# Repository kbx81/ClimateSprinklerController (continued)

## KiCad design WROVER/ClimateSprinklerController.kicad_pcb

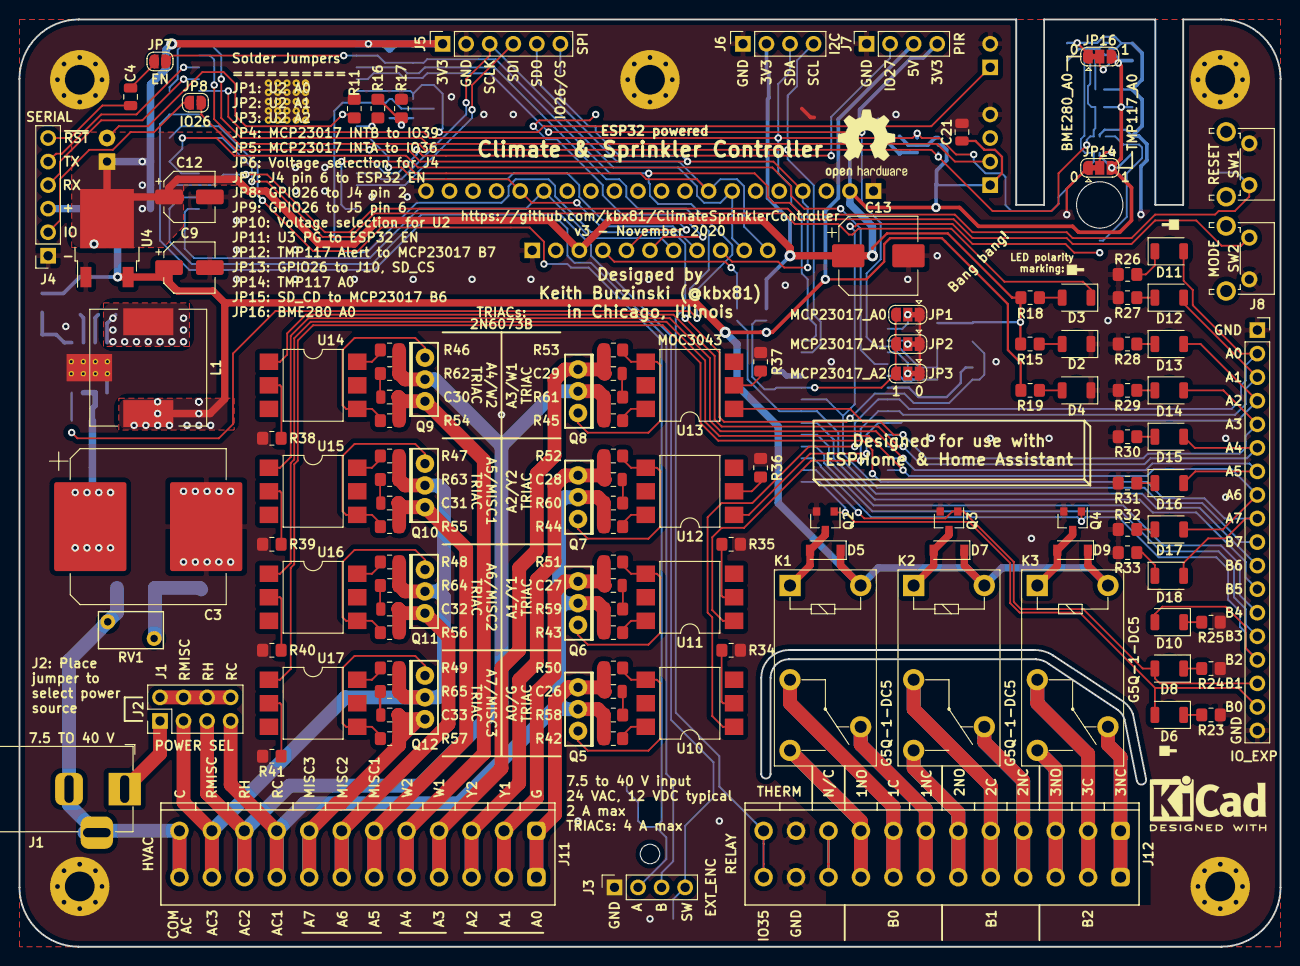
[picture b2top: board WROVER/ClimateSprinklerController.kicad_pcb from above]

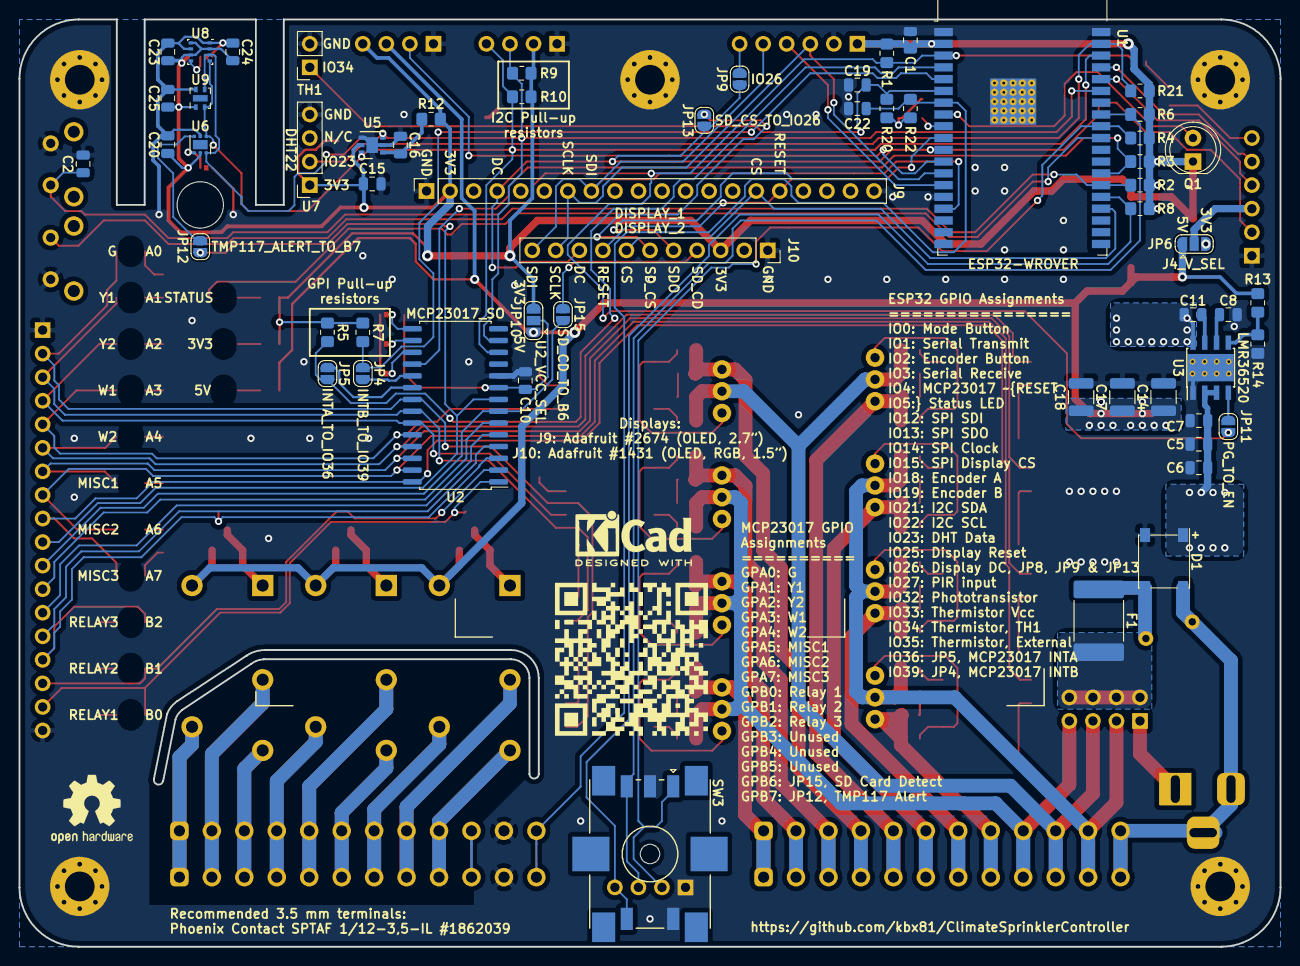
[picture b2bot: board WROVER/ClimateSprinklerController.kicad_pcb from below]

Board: 2 copper layers, 136.0 x 100.0 mm, 190 parts (61 on the bottom side), 141 nets.

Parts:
C1: 10 uF; C_0805_2012Metric
C2, C4, C10, C11, C19, C20, C21, C22, C23, C24, C25: 100 nF; C_0805_2012Metric
C3: 470 uF; CP_Elec_16x17.5
C5, C6: 4.7 uF; C_0805_2012Metric
C7: 220 nF; C_0805_2012Metric
C8, C15, C16: 1 uF; C_0805_2012Metric
C9, C12: 10 uF; CP_Elec_5x5.8
C13: 220 uF; CP_Elec_8x10
C14, C17, C18: 47 uF; C_1210_3225Metric
C26, C27, C28, C29, C30, C31, C32, C33: .01 uF; C_0805_2012Metric
D1: N/A; Diode_Bridge_Bourns_CD-MBL2xxS
D2: 3V3; LED_1206_3216Metric_ReverseMount_Hole1.8x2.4mm
D3: STATUS; LED_1206_3216Metric_ReverseMount_Hole1.8x2.4mm
D4: 5V; LED_1206_3216Metric_ReverseMount_Hole1.8x2.4mm
D5, D7, D9: N/A; D_SOD-123
D6: RELAY1; LED_1206_3216Metric_ReverseMount_Hole1.8x2.4mm
D8: RELAY2; LED_1206_3216Metric_ReverseMount_Hole1.8x2.4mm
D10: RELAY3; LED_1206_3216Metric_ReverseMount_Hole1.8x2.4mm
D11: G; LED_1206_3216Metric_ReverseMount_Hole1.8x2.4mm
D12: Y1; LED_1206_3216Metric_ReverseMount_Hole1.8x2.4mm
D13: Y2; LED_1206_3216Metric_ReverseMount_Hole1.8x2.4mm
D14: W1; LED_1206_3216Metric_ReverseMount_Hole1.8x2.4mm
D15: W2; LED_1206_3216Metric_ReverseMount_Hole1.8x2.4mm
D16: MISC1; LED_1206_3216Metric_ReverseMount_Hole1.8x2.4mm
D17: MISC2; LED_1206_3216Metric_ReverseMount_Hole1.8x2.4mm
D18: MISC3; LED_1206_3216Metric_ReverseMount_Hole1.8x2.4mm
F1: 300 mA; Fuse_2920_7451Metric
H1, H2, H3, H4, H5: MountingHole_Pad; MountingHole_3.2mm_M3_Pad_Via
H6: MountingHole; MountingHole_5mm
J1: 7.5 TO 40 V; BarrelJack_Horizontal
J2: POWER SEL; PinHeader_2x04_P2.54mm_Vertical
J3: EXT_ENC; PinSocket_1x04_P2.54mm_Vertical
J4: SERIAL; PinSocket_1x06_P2.54mm_Vertical
J5: SPI; PinSocket_1x06_P2.54mm_Vertical
J6: I2C; PinSocket_1x04_P2.54mm_Vertical
J7: PIR; PinSocket_1x04_P2.54mm_Vertical
J8: IO_EXP; PinSocket_1x18_P2.54mm_Vertical
J9: DISPLAY_1; PinSocket_1x20_P2.54mm_Vertical
J10: DISPLAY_2; PinSocket_1x11_P2.54mm_Vertical
J11: HVAC; PhoenixContact_SPTAF_1_12-3.5-IL_1x12_P3.50mm_Vertical
J12: RELAY; PhoenixContact_SPTAF_1_12-3.5-IL_1x12_P3.50mm_Vertical
JP1: MCP23017_A0; SolderJumper-3_P1.3mm_Bridged12_RoundedPad1.0x1.5mm
JP2: MCP23017_A1; SolderJumper-3_P1.3mm_Bridged12_RoundedPad1.0x1.5mm
JP3: MCP23017_A2; SolderJumper-3_P1.3mm_Bridged12_RoundedPad1.0x1.5mm
JP4: INTB_TO_IO39; SolderJumper-2_P1.3mm_Open_RoundedPad1.0x1.5mm
JP5: INTA_TO_IO36; SolderJumper-2_P1.3mm_Open_RoundedPad1.0x1.5mm
JP6: J4_V_SEL; SolderJumper-3_P1.3mm_Open_RoundedPad1.0x1.5mm
JP7: EN; SolderJumper-2_P1.3mm_Open_RoundedPad1.0x1.5mm
JP8, JP9: IO26; SolderJumper-2_P1.3mm_Open_RoundedPad1.0x1.5mm
JP10: U2_VCC_SEL; SolderJumper-3_P1.3mm_Open_RoundedPad1.0x1.5mm
JP11: PG_TO_EN; SolderJumper-2_P1.3mm_Open_RoundedPad1.0x1.5mm
JP12: TMP117_ALERT_TO_B7; SolderJumper-2_P1.3mm_Open_RoundedPad1.0x1.5mm
JP13: SD_CS_TO_IO26; SolderJumper-2_P1.3mm_Open_RoundedPad1.0x1.5mm
JP14: TMP117_A0; SolderJumper-3_P1.3mm_Bridged12_RoundedPad1.0x1.5mm
JP15: SD_CD_TO_B6; SolderJumper-2_P1.3mm_Open_RoundedPad1.0x1.5mm
JP16: BME280_A0; SolderJumper-3_P1.3mm_Bridged12_RoundedPad1.0x1.5mm
K1, K2, K3: G5Q-1-DC5; Relay_SPDT_Omron-G5Q-1
L1: 15 uH; L_Wuerth_WE-PD-Typ-LS
Q1: TEPT5700; LED_D5.0mm_Clear
Q2, Q3, Q4: 2N7002; SOT-23
Q5, Q6, Q7, Q8, Q9, Q10, Q11, Q12: 2N6073B; TO-225-3_Vertical
QR*****: ClimateSprinklerControllerQR
R1, R2, R3, R4, R5, R6, R7, R8, R16, R20, R21, R22, R26: 10K; R_0805_2012Metric_Pad1.20x1.40mm_HandSolder
R9, R10: 3K3; R_0805_2012Metric_Pad1.20x1.40mm_HandSolder
R11, R13: 100K; R_0805_2012Metric_Pad1.20x1.40mm_HandSolder
R12: 4.7; R_0805_2012Metric_Pad1.20x1.40mm_HandSolder
R14: 24.9K; R_0805_2012Metric_Pad1.20x1.40mm_HandSolder
R15: 1K6; R_0805_2012Metric_Pad1.20x1.40mm_HandSolder
R17: 5K; R_0805_2012Metric_Pad1.20x1.40mm_HandSolder
R18: 120; R_0805_2012Metric_Pad1.20x1.40mm_HandSolder
R19: 8K2; R_0805_2012Metric_Pad1.20x1.40mm_HandSolder
R23, R24, R25: 560; R_0805_2012Metric_Pad1.20x1.40mm_HandSolder
R27, R28, R31, R32, R33: 1K5; R_0805_2012Metric_Pad1.20x1.40mm_HandSolder
R29, R30: 2K7; R_0805_2012Metric_Pad1.20x1.40mm_HandSolder
R34, R35, R36, R37, R38, R39, R40, R41: 270; R_0805_2012Metric_Pad1.20x1.40mm_HandSolder
R42, R43, R44, R45, R46, R47, R48, R49: 180; R_0805_2012Metric_Pad1.20x1.40mm_HandSolder
R50, R51, R52, R53, R54, R55, R56, R57: 820; R_0805_2012Metric_Pad1.20x1.40mm_HandSolder
R58, R59, R60, R61, R62, R63, R64, R65: 39; R_0805_2012Metric_Pad1.20x1.40mm_HandSolder
RV1: N/A; RV_Disc_D7mm_W4mm_P5mm
SW1: RESET; SW_Tactile_SPST_Angled_PTS645Vx58-2LFS
SW2: MODE; SW_Tactile_SPST_Angled_PTS645Vx58-2LFS
SW3: PEC11S-929K-S0015; RotaryEncoder_Bourns_PEC11S-Switch_Vertical_H9.5mm
TH1: 10K; PinSocket_1x02_P2.54mm_Vertical
U1: ESP32-WROVER
U2: MCP23017_SO; SOIC-28W_7.5x17.9mm_P1.27mm
U3: LMR36520; Texas_HSOP-8-1EP_3.9x4.9mm_P1.27mm_ThermalVias
U4: LD1086DT33TR; TO-252-2
U5: SGP40-Sensor_Air_Quality; DFN-6-1EP_2.44x2.44mm_P0.8mm_EP1.25x1.7mm
U6: TMP117; WSON-6-1EP_2x2mm_P0.65mm_EP1x1.6mm
U7: DHT22; PinSocket_1x04_P2.54mm_Vertical
U8: BME280; Bosch_LGA-8_2.5x2.5mm_P0.65mm_ClockwisePinNumbering
U9: SHTC3; AMS_QFN-4-1EP_2x2mm_P0.95mm_EP0.7x1.6mm
U10, U11, U12, U13, U14, U15, U16, U17: MOC3043; SMDIP-6_W9.53mm

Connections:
+3V3: C1.2, C12.1, C13.1, C15.2, C20.1, C21.1, C23.1, C24.1, C25.1, J5.1, J6.2, J7.4, J9.2, J10.3, JP6.3, JP10.3, JP14.3, JP16.3, Q1.1, R1.2, R2.2, R3.1, R4.1, R5.1, R6.1, R7.1, R8.1, R9.1, R10.1, R12.1, R15.1, R18.1, R21.2, U1.2, U4.2, U5.5, U6.5, U7.1, U8.2, U8.6, U8.8, U9.1
+5V: C9.1, C14.1, C17.1, C18.1, D5.1, D7.1, D9.1, J7.3, JP6.1, JP10.1, K1.5, K2.5, K3.5, L1.2, R13.1, R19.2, U4.3
+VDC: C3.1, C5.1, C6.1, C7.1, D1.1, U3.2, U3.3
/C_TERM: D1.2, J1.2, J1.3, J11.12, RV1.2
/DHT_DATA: R21.1, U1.37, U7.2
/DISP_CS: J9.15, J10.7, U1.23
/DISP_D0_SCLK: J5.3, J9.7, J10.10, U1.13
/DISP_D1_DIN: J5.5, J9.8, J10.11, U1.16
/DISP_DC: J9.4, J10.9, JP8.2, JP9.2, JP13.2, U1.11
/DISP_RESET: J9.16, J10.8, U1.10
/ENCODER_A: J3.2, R4.2, SW3.A, U1.30
/ENCODER_B: J3.3, R6.2, SW3.B, U1.31
/ENCODER_SW: J3.4, R8.2, SW3.S2, U1.24
/ESP_MISO: J5.4, J10.5, U1.14
/ESP_RXD: J4.4, U1.34
/ESP_TXD: J4.5, U1.35
/G_TERM: C26.2, J11.1, Q5.1, R50.2
/I2C_SCL: J6.4, R10.2, U1.36, U2.12, U5.6, U6.1, U8.4, U9.2
/I2C_SDA: J6.3, R9.2, U1.33, U2.13, U5.3, U6.6, U8.3, U9.3
/MCP23017_A0: JP1.2, U2.15
/MCP23017_A1: JP2.2, U2.16
/MCP23017_A2: JP3.2, U2.17
/MCP23017_GPA0: D11.2, J8.2, U2.21, U10.1
/MCP23017_GPA1: D12.2, J8.3, U2.22, U11.1
/MCP23017_GPA2: D13.2, J8.4, U2.23, U12.1
/MCP23017_GPA3: D14.2, J8.5, U2.24, U13.1
/MCP23017_GPA4: D15.2, J8.6, U2.25, U14.1
/MCP23017_GPA5: D16.2, J8.7, U2.26, U15.1
/MCP23017_GPA6: D17.2, J8.8, U2.27, U16.1
/MCP23017_GPA7: D18.2, J8.9, U2.28, U17.1
/MCP23017_GPB0: D6.2, J8.17, Q2.1, U2.1
/MCP23017_GPB1: D8.2, J8.16, Q3.1, U2.2
/MCP23017_GPB2: D10.2, J8.15, Q4.1, U2.3
/MCP23017_GPB3: J8.14, U2.4
/MCP23017_GPB4: J8.13, U2.5
/MCP23017_GPB5: J8.12, U2.6
/MCP23017_GPB6: J8.11, JP15.2, U2.7
/MCP23017_GPB7: J8.10, JP12.2, U2.8
/MCP23017_INTA: JP5.2, R5.2, U1.4
/MCP23017_INTB: JP4.2, R7.2, U1.5
/MCP23017_~RESET: R3.2, U1.26, U2.18
/MISC1_TERM: C31.2, J11.6, Q10.1, R55.2
/MISC2_TERM: C32.2, J11.7, Q11.1, R56.2
/MISC3_TERM: C33.2, J11.8, Q12.1, R57.2
/MODE: R2.1, SW2.1, U1.25
/PHOTO: Q1.2, R11.2, U1.8
/PIR: J7.2, U1.12
/RC_TERM: J2.7, J11.9, Q5.2, Q6.2, Q7.2, R42.1, R43.1, R44.1, R58.1, R59.1, R60.1
/RELAY_1_COM_TERM: J12.8, K1.2
/RELAY_1_NC_TERM: J12.7, K1.4
/RELAY_1_NO_TERM: J12.9, K1.3
/RELAY_2_COM_TERM: J12.5, K2.2
/RELAY_2_NC_TERM: J12.4, K2.4
/RELAY_2_NO_TERM: J12.6, K2.3
/RELAY_3_COM_TERM: J12.2, K3.2
/RELAY_3_NC_TERM: J12.1, K3.4
/RELAY_3_NO_TERM: J12.3, K3.3
/RH_TERM: J2.5, J11.10, Q8.2, Q9.2, R45.1, R46.1, R61.1, R62.1
/RMISC_TERM: J2.3, J11.11, Q10.2, Q11.2, Q12.2, R47.1, R48.1, R49.1, R63.1, R64.1, R65.1
/SD_CD: J10.4, JP15.1
/SD_CS: J10.6, JP13.1
/STATUS: D3.1, U1.29
/THERMISTOR_1V1: R16.1, R17.2, R20.2, R22.1
/THERMISTOR_EXT: C22.1, J12.12, R22.2, U1.7
/THERMISTOR_INT: C19.1, R20.1, TH1.1, U1.6
/THERMISTOR_VCC: R16.2, U1.9
/TMP117_ALERT: JP12.1, U6.3
/W1_TERM: C29.2, J11.4, Q8.1, R53.2
/W2_TERM: C30.2, J11.5, Q9.1, R54.2
/Y1_TERM: C27.2, J11.2, Q6.1, R51.2
/Y2_TERM: C28.2, J11.3, Q7.1, R52.2
/~ESP_RESET: C2.1, JP7.2, JP11.1, R1.1, SW1.2, U1.3
GND: C1.1, C2.2, C3.2, C5.2, C6.2, C7.2, C8.2, C9.2, C10.2, C12.2, C13.2, C14.2, C15.1, C16.1, C17.2, C18.2, C19.2, C20.2, C21.2, C22.2, C23.2, C24.2, C25.2, D1.4, D2.1, D4.1, H1.1, H2.1, H3.1, H4.1, H5.1, J3.1, J4.1, J5.2, J6.1, J7.1, J8.1, J8.18, J9.1, J9.20, J10.1, J12.11, JP1.1, JP2.1, JP3.1, JP14.1, JP16.1, Q2.2, Q3.2, Q4.2, R11.1, R14.2, R17.1, R23.1, R24.1, R25.1, R26.2, R27.2, R28.2, R29.2, R30.2, R31.2, R32.2, R33.2, R34.2, R35.2, R36.2, R37.2, R38.2, R39.2, R40.2, R41.2, SW1.1, SW2.2, SW3.C, SW3.S1, TH1.2, U1.1, U1.15, U1.38, U1.39, U2.10, U3.1, U3.9, U4.1, U5.2, U5.4, U5.7, U6.2, U7.4, U8.1, U8.7, U9.4
unnamed: C4.1, JP7.1
unnamed: C4.2, J4.6
unnamed: C8.1, U3.6
unnamed: C10.1, JP1.3, JP2.3, JP3.3, JP10.2, U2.9
unnamed: C11.1, U3.7
unnamed: C11.2, L1.1, U3.8
unnamed: C16.2, R12.2, U5.1
unnamed: C26.1, R58.2
unnamed: C27.1, R59.2
unnamed: C28.1, R60.2
unnamed: C29.1, R61.2
unnamed: C30.1, R62.2
unnamed: C31.1, R63.2
unnamed: C32.1, R64.2
unnamed: C33.1, R65.2
unnamed: D1.3, F1.2, RV1.1
unnamed: D2.2, R15.2
unnamed: D3.2, R18.2
unnamed: D4.2, R19.1
unnamed: D5.2, K1.1, Q2.3
unnamed: D6.1, R23.2
unnamed: D7.2, K2.1, Q3.3
unnamed: D8.1, R24.2
unnamed: D9.2, K3.1, Q4.3
unnamed: D10.1, R25.2
unnamed: D11.1, R26.1
unnamed: D12.1, R27.1
unnamed: D13.1, R28.1
unnamed: D14.1, R29.1
unnamed: D15.1, R30.1
unnamed: D16.1, R31.1
unnamed: D17.1, R32.1
unnamed: D18.1, R33.1
unnamed: F1.1, J2.2, J2.4, J2.6, J2.8
unnamed: J1.1, J2.1
unnamed: J4.2, JP8.1
unnamed: J4.3, JP6.2
unnamed: J5.6, JP9.1
unnamed: JP4.1, U2.19
unnamed: JP5.1, U2.20
unnamed: JP11.2, U3.4
unnamed: JP14.2, U6.4
unnamed: JP16.2, U8.5
unnamed: Q5.3, R50.1, U10.4
unnamed: Q6.3, R51.1, U11.4
unnamed: Q7.3, R52.1, U12.4
unnamed: Q8.3, R53.1, U13.4
unnamed: Q9.3, R54.1, U14.4
unnamed: Q10.3, R55.1, U15.4
unnamed: Q11.3, R56.1, U16.4
unnamed: Q12.3, R57.1, U17.4
unnamed: R13.2, R14.1, U3.5
unnamed: R34.1, U10.2
unnamed: R35.1, U11.2
unnamed: R36.1, U12.2
unnamed: R37.1, U13.2
unnamed: R38.1, U14.2
unnamed: R39.1, U15.2
unnamed: R40.1, U16.2
unnamed: R41.1, U17.2
unnamed: R42.2, U10.6
unnamed: R43.2, U11.6
unnamed: R44.2, U12.6
unnamed: R45.2, U13.6
unnamed: R46.2, U14.6
unnamed: R47.2, U15.6
unnamed: R48.2, U16.6
unnamed: R49.2, U17.6

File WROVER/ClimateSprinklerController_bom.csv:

Component,Quantity Per PCB,References,Value,MPN1,MPN2,Footprint,Population
1,8,C26 C27 C28 C29 C30 C31 C32 C33,.01 uF,CC0805KRX7R9BB103,,C_0805_2012Metric,
2,11,C2 C4 C10 C11 C19 C20 C21 C22 C23 C24 C25,100 nF,CC0805KRX7R7BB104,,C_0805_2012Metric,
3,1,C7,220 nF,C2012X5R1H224K125AA,,C_0805_2012Metric,
4,3,C8 C15 C16,1 uF,C0805C105K4RACTU,,C_0805_2012Metric,
5,2,C5 C6,4.7 uF,C2012X5R1H475K125AB,,C_0805_2012Metric,
6,1,C1,10 uF,C2012X5R1V106K085AC,,C_0805_2012Metric,
7,2,C9 C12,10 uF,EEE-HP0J100R,,CP_Elec_5x5.8,
8,3,C14 C17 C18,47 uF,GRM32ER61C476KE15L,,C_1210_3225Metric,
9,1,C13,220 uF,EEE-HB0J221AP,,CP_Elec_8x10,
10,1,C3,470 uF,EEV-FK1H471M,,CP_Elec_16x17.5,
11,1,D1,N/A,CD-MBL206SL,,Diode_Bridge_Bourns_CD-MBL2xxS,
12,3,D5 D7 D9,N/A,1N4148W,,D_SOD-123,
13,1,F1,300 mA,2920L030DR,,Fuse_2920_7451Metric,
14,1,J1,7.5 TO 40 V,694106301002,,BarrelJack_Horizontal,
15,2,J11 J12,HVAC,1862039,,PhoenixContact_SPTAF_1_12-3.5-IL_1x12_P3.50mm_Vertical,
16,3,K1 K2 K3,G5Q-1-DC5,G5Q-1-DC5,,Relay_SPDT_Omron-G5Q-1,
17,1,L1,15 uH,7447709150,MSS1210-153MEB,L_Wuerth_WE-PD-Typ-LS,
18,8,Q5 Q6 Q7 Q8 Q9 Q10 Q11 Q12,2N6073B,2N6073BG,,TO-225-3_Vertical,
19,3,Q2 Q3 Q4,2N7002,2N7002,,SOT-23,
20,1,Q1,TEPT5700,TEPT5700,,LED_D5.0mm_Clear,
21,1,R12,4.7,RC0805FR-07100KL,,R_0805_2012Metric_Pad1.20x1.40mm_HandSolder,
22,8,R58 R59 R60 R61 R62 R63 R64 R65,39,ERJ-P06J390V,,R_0805_2012Metric_Pad1.20x1.40mm_HandSolder,
23,1,R18,120,RT0805FRE07120RL,,R_0805_2012Metric_Pad1.20x1.40mm_HandSolder,
24,8,R42 R43 R44 R45 R46 R47 R48 R49,180,RT0805FRE07180RL,,R_0805_2012Metric_Pad1.20x1.40mm_HandSolder,
25,8,R34 R35 R36 R37 R38 R39 R40 R41,270,RT0805FRE07270RL,,R_0805_2012Metric_Pad1.20x1.40mm_HandSolder,
26,3,R23 R24 R25,560,RT0805FRE07560RL,,R_0805_2012Metric_Pad1.20x1.40mm_HandSolder,
27,8,R50 R51 R52 R53 R54 R55 R56 R57,820,RT0805FRE07820RL,,R_0805_2012Metric_Pad1.20x1.40mm_HandSolder,
28,5,R27 R28 R31 R32 R33,1K5,RT0805FRE071K5L,,R_0805_2012Metric_Pad1.20x1.40mm_HandSolder,
29,1,R15,1K6,RT0805FRE071K6L,,R_0805_2012Metric_Pad1.20x1.40mm_HandSolder,
30,2,R29 R30,2K7,RT0805FRE072K7L,,R_0805_2012Metric_Pad1.20x1.40mm_HandSolder,
31,2,R9 R10,3K3,RT0805FRE073K3L,,R_0805_2012Metric_Pad1.20x1.40mm_HandSolder,
32,1,R17,5K,CRCW08055K00JNTA,,R_0805_2012Metric_Pad1.20x1.40mm_HandSolder,
33,1,R19,8K2,RT0805FRE078K2L,,R_0805_2012Metric_Pad1.20x1.40mm_HandSolder,
34,13,R1 R2 R3 R4 R5 R6 R7 R8 R16 R20 R21 R22 R26,10K,RC0805FR-0710KL,,R_0805_2012Metric_Pad1.20x1.40mm_HandSolder,
35,1,R14,24.9K,RT0805FRE0724K9L,,R_0805_2012Metric_Pad1.20x1.40mm_HandSolder,
36,2,R11 R13,100K,RC0805FR-07100KL,,R_0805_2012Metric_Pad1.20x1.40mm_HandSolder,
37,1,RV1,N/A,B72205S0400K101,,RV_Disc_D7mm_W4mm_P5mm,
38,1,SW2,MODE,PTS645VK582LFS,,SW_Tactile_SPST_Angled_PTS645Vx58-2LFS,
39,1,SW3,PEC11S-929K-S0015,PEC11S-929K-S0015,,RotaryEncoder_Bourns_PEC11S-Switch_Vertical_H9.5mm,
40,1,SW1,RESET,PTS645VK582LFS,,SW_Tactile_SPST_Angled_PTS645Vx58-2LFS,
41,1,TH1,10K,NXFT15XH103FA2B100,,PinSocket_1x02_P2.54mm_Vertical,
42,1,U8,BME280,BME280,,Bosch_LGA-8_2.5x2.5mm_P0.65mm_ClockwisePinNumbering,
43,1,U7,DHT22,DHT22,,PinSocket_1x04_P2.54mm_Vertical,
44,1,U1,ESP32-WROVER,ESP32-WROVER,,ESP32-WROVER,
45,1,U4,LD1086DT33TR,LD1086DT33TR,,TO-252-2,
46,1,U3,LMR36520,LMR36520ADDAR,,Texas_HSOP-8-1EP_3.9x4.9mm_P1.27mm_ThermalVias,
47,1,U2,MCP23017_SO,MCP23017-E/SO,,SOIC-28W_7.5x17.9mm_P1.27mm,
48,8,U10 U11 U12 U13 U14 U15 U16 U17,MOC3043,MOC3043SM,,SMDIP-6_W9.53mm,
49,1,U5,SGP40,SGP40,,DFN-6-1EP_2.44x2.44mm_P0.8mm_EP1.25x1.7mm,
50,1,U9,SHTC3,SHTC3,,AMS_QFN-4-1EP_2x2mm_P0.95mm_EP0.7x1.6mm,
51,1,U6,TMP117,TMP117MAIDRVR,,WSON-6-1EP_2x2mm_P0.65mm_EP1x1.6mm,





Component Groups:,67
Component Count:,164
Fitted Components:,144
Number of PCBs:,1
Total components:,144
Schematic Version:,2
Schematic Date:,2020-08-14
PCB Variant:,udefault
BoM Date:,"Thursday, March 25, 2021 at 01:11:38 AM"
Schematic Source:,ClimateSprinklerController.sch
KiCad Version:,Eeschema (5.1.9-0-10_14)

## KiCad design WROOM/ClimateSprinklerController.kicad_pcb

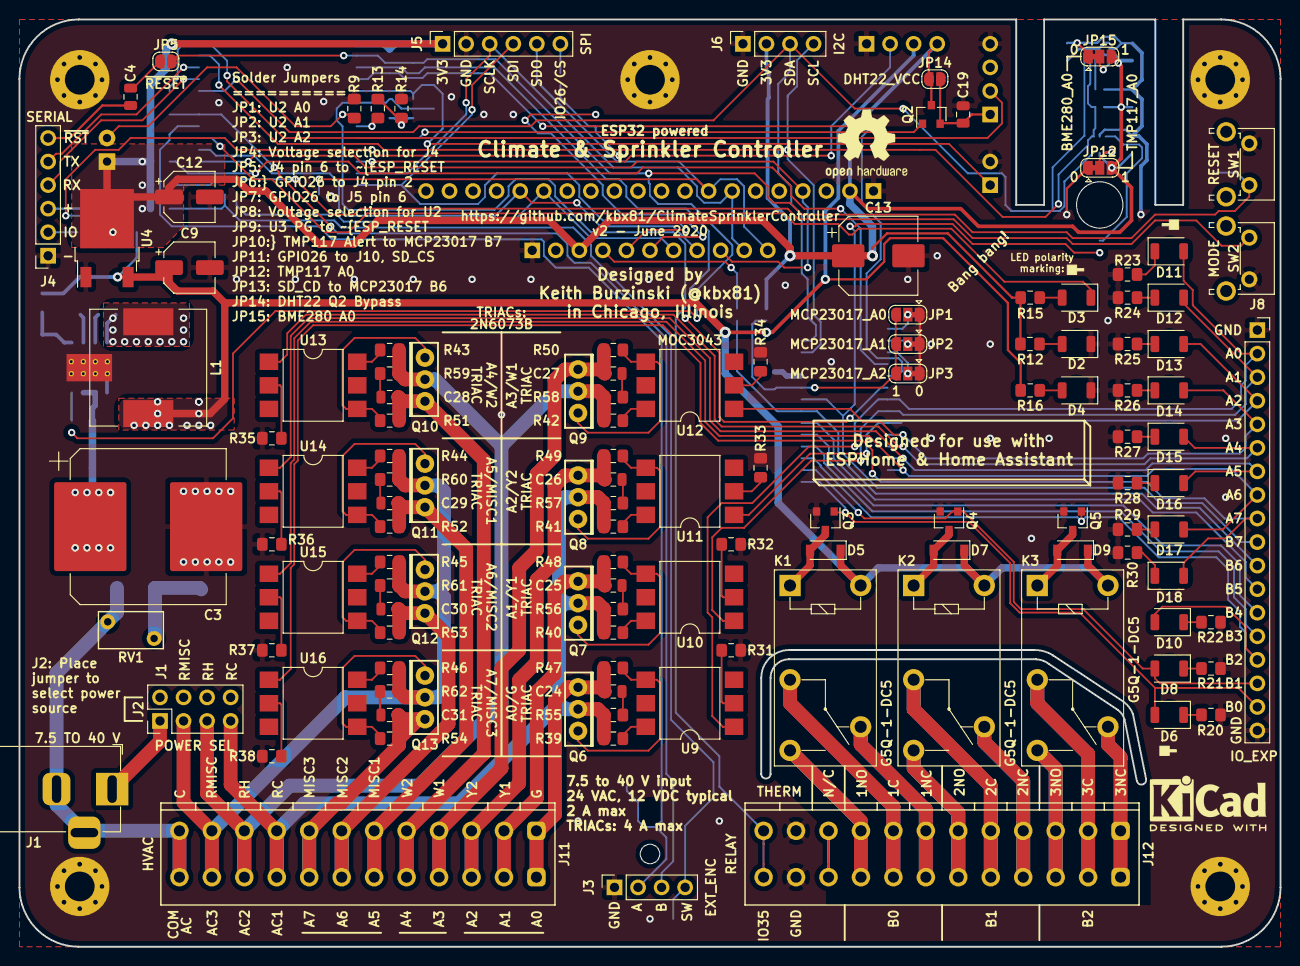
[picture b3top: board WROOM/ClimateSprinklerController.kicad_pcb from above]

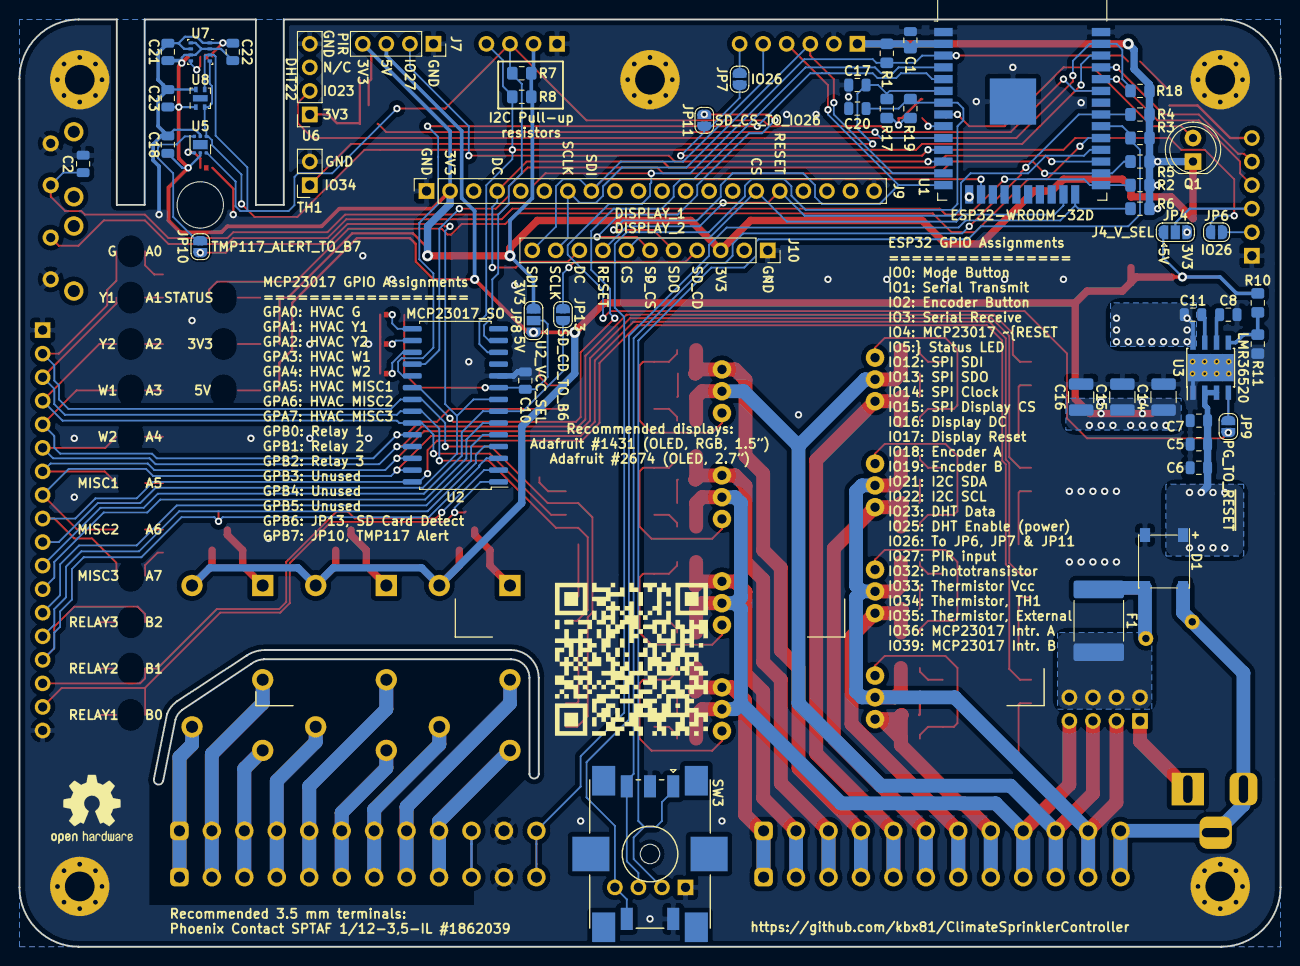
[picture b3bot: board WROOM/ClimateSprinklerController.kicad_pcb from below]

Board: 2 copper layers, 136.0 x 100.0 mm, 184 parts (55 on the bottom side), 141 nets.

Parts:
C1: 10 uF; C_0805_2012Metric
C2, C4, C10, C11, C17, C18, C19, C20, C21, C22, C23: 100 nF; C_0805_2012Metric
C3: 470 uF; CP_Elec_16x17.5
C5, C6: 4.7 uF; C_0805_2012Metric
C7: 220 nF; C_0805_2012Metric
C8: 1 uF; C_0805_2012Metric
C9, C12: 10 uF; CP_Elec_5x5.8
C13: 220 uF; CP_Elec_8x10
C14, C15, C16: 47 uF; C_1210_3225Metric
C24, C25, C26, C27, C28, C29, C30, C31: .01 uF; C_0805_2012Metric
D1: N/A; Diode_Bridge_Bourns_CD-MBL2xxS
D2: 3V3; LED_1206_3216Metric_ReverseMount_Hole1.8x2.4mm
D3: STATUS; LED_1206_3216Metric_ReverseMount_Hole1.8x2.4mm
D4: 5V; LED_1206_3216Metric_ReverseMount_Hole1.8x2.4mm
D5, D7, D9: N/A; D_SOD-123
D6: RELAY1; LED_1206_3216Metric_ReverseMount_Hole1.8x2.4mm
D8: RELAY2; LED_1206_3216Metric_ReverseMount_Hole1.8x2.4mm
D10: RELAY3; LED_1206_3216Metric_ReverseMount_Hole1.8x2.4mm
D11: G; LED_1206_3216Metric_ReverseMount_Hole1.8x2.4mm
D12: Y1; LED_1206_3216Metric_ReverseMount_Hole1.8x2.4mm
D13: Y2; LED_1206_3216Metric_ReverseMount_Hole1.8x2.4mm
D14: W1; LED_1206_3216Metric_ReverseMount_Hole1.8x2.4mm
D15: W2; LED_1206_3216Metric_ReverseMount_Hole1.8x2.4mm
D16: MISC1; LED_1206_3216Metric_ReverseMount_Hole1.8x2.4mm
D17: MISC2; LED_1206_3216Metric_ReverseMount_Hole1.8x2.4mm
D18: MISC3; LED_1206_3216Metric_ReverseMount_Hole1.8x2.4mm
F1: 300 mA; Fuse_2920_7451Metric
H1, H2, H3, H4, H5: MountingHole_Pad; MountingHole_3.2mm_M3_Pad_Via
H6: MountingHole; MountingHole_5mm
J1: 7.5 TO 40 V; BarrelJack_Horizontal
J2: POWER SEL; PinHeader_2x04_P2.54mm_Vertical
J3: EXT_ENC; PinSocket_1x04_P2.54mm_Vertical
J4: SERIAL; PinSocket_1x06_P2.54mm_Vertical
J5: SPI; PinSocket_1x06_P2.54mm_Vertical
J6: I2C; PinSocket_1x04_P2.54mm_Vertical
J7: PIR; PinSocket_1x04_P2.54mm_Vertical
J8: IO_EXP; PinSocket_1x18_P2.54mm_Vertical
J9: DISPLAY_1; PinSocket_1x20_P2.54mm_Vertical
J10: DISPLAY_2; PinSocket_1x11_P2.54mm_Vertical
J11: HVAC; PhoenixContact_SPTAF_1_12-3.5-IL_1x12_P3.50mm_Vertical
J12: RELAY; PhoenixContact_SPTAF_1_12-3.5-IL_1x12_P3.50mm_Vertical
JP1: MCP23017_A0; SolderJumper-3_P1.3mm_Bridged12_RoundedPad1.0x1.5mm
JP2: MCP23017_A1; SolderJumper-3_P1.3mm_Bridged12_RoundedPad1.0x1.5mm
JP3: MCP23017_A2; SolderJumper-3_P1.3mm_Bridged12_RoundedPad1.0x1.5mm
JP4: J4_V_SEL; SolderJumper-3_P1.3mm_Open_RoundedPad1.0x1.5mm
JP5: ~RESET; SolderJumper-2_P1.3mm_Open_RoundedPad1.0x1.5mm
JP6, JP7: IO26; SolderJumper-2_P1.3mm_Open_RoundedPad1.0x1.5mm
JP8: U2_VCC_SEL; SolderJumper-3_P1.3mm_Open_RoundedPad1.0x1.5mm
JP9: PG_TO_~RESET; SolderJumper-2_P1.3mm_Open_RoundedPad1.0x1.5mm
JP10: TMP117_ALERT_TO_B7; SolderJumper-2_P1.3mm_Open_RoundedPad1.0x1.5mm
JP11: SD_CS_TO_IO26; SolderJumper-2_P1.3mm_Open_RoundedPad1.0x1.5mm
JP12: TMP117_A0; SolderJumper-3_P1.3mm_Bridged12_RoundedPad1.0x1.5mm
JP13: SD_CD_TO_B6; SolderJumper-2_P1.3mm_Open_RoundedPad1.0x1.5mm
JP14: DHT22_VCC; SolderJumper-2_P1.3mm_Open_RoundedPad1.0x1.5mm
JP15: BME280_A0; SolderJumper-3_P1.3mm_Bridged12_RoundedPad1.0x1.5mm
K1, K2, K3: G5Q-1-DC5; Relay_SPDT_Omron-G5Q-1
L1: 15 uH; L_Wuerth_WE-PD-Typ-LS
Q1: TEPT5700; LED_D5.0mm_Clear
Q2, Q3, Q4, Q5: 2N7002; SOT-23
Q6, Q7, Q8, Q9, Q10, Q11, Q12, Q13: 2N6073B; TO-225-3_Vertical
QR*****: ClimateSprinklerControllerQR
R1, R2, R3, R4, R5, R6, R13, R17, R18, R19, R23: 10K; R_0805_2012Metric_Pad1.15x1.40mm_HandSolder
R7, R8: 3K3; R_0805_2012Metric_Pad1.15x1.40mm_HandSolder
R9, R10: 100K; R_0805_2012Metric_Pad1.15x1.40mm_HandSolder
R11: 24.9K; R_0805_2012Metric_Pad1.15x1.40mm_HandSolder
R12: 1K6; R_0805_2012Metric_Pad1.15x1.40mm_HandSolder
R14: 5K; R_0805_2012Metric_Pad1.15x1.40mm_HandSolder
R15: 120; R_0805_2012Metric_Pad1.15x1.40mm_HandSolder
R16: 8K2; R_0805_2012Metric_Pad1.15x1.40mm_HandSolder
R20, R21, R22: 560; R_0805_2012Metric_Pad1.15x1.40mm_HandSolder
R24, R25, R28, R29, R30: 1K5; R_0805_2012Metric_Pad1.15x1.40mm_HandSolder
R26, R27: 2K7; R_0805_2012Metric_Pad1.15x1.40mm_HandSolder
R31, R32, R33, R34, R35, R36, R37, R38: 270; R_0805_2012Metric_Pad1.15x1.40mm_HandSolder
R39, R40, R41, R42, R43, R44, R45, R46: 180; R_0805_2012Metric_Pad1.15x1.40mm_HandSolder
R47, R48, R49, R50, R51, R52, R53, R54: 820; R_0805_2012Metric_Pad1.15x1.40mm_HandSolder
R55, R56, R57, R58, R59, R60, R61, R62: 39; R_0805_2012Metric_Pad1.15x1.40mm_HandSolder
RV1: N/A; RV_Disc_D7mm_W4mm_P5mm
SW1: RESET; SW_Tactile_SPST_Angled_PTS645Vx58-2LFS
SW2: MODE; SW_Tactile_SPST_Angled_PTS645Vx58-2LFS
SW3: PEC11S-929K-S0015; RotaryEncoder_Bourns_PEC11S-Switch_Vertical_H9.5mm
TH1: 10K; PinSocket_1x02_P2.54mm_Vertical
U1: ESP32-WROOM-32D; ESP32-WROOM-32
U2: MCP23017_SO; SOIC-28W_7.5x17.9mm_P1.27mm
U3: LMR36520; Texas_HSOP-8-1EP_3.9x4.9mm_P1.27mm_ThermalVias
U4: LD1086DT33TR; TO-252-2
U5: TMP117; WSON-6-1EP_2x2mm_P0.65mm_EP1x1.6mm
U6: DHT22; PinSocket_1x04_P2.54mm_Vertical
U7: BME280; Bosch_LGA-8_2.5x2.5mm_P0.65mm_ClockwisePinNumbering
U8: SHTC3; AMS_QFN-4-1EP_2x2mm_P0.95mm_EP0.7x1.6mm
U9, U10, U11, U12, U13, U14, U15, U16: MOC3043; SMDIP-6_W9.53mm

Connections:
+3V3: C1.2, C12.1, C13.1, C18.1, C21.1, C22.1, C23.1, J5.1, J6.2, J7.4, J9.2, J10.3, JP4.3, JP8.3, JP12.3, JP14.1, JP15.3, Q1.1, Q2.3, R1.2, R2.2, R3.1, R4.1, R5.1, R6.1, R7.1, R8.1, R12.1, R15.1, R18.2, U1.2, U4.2, U5.5, U7.2, U7.6, U7.8, U8.1
+5V: C9.1, C14.1, C15.1, C16.1, D5.1, D7.1, D9.1, J7.3, JP4.1, JP8.1, K1.5, K2.5, K3.5, L1.2, R10.1, R16.2, U4.3
+VDC: C3.1, C5.1, C6.1, C7.1, D1.1, U3.2, U3.3
/C_TERM: D1.2, J1.2, J1.3, J11.12, RV1.2
/DHT_DATA: R18.1, U1.37, U6.2
/DHT_EN: Q2.1, U1.10
/DISP_CS: J9.15, J10.7, U1.23
/DISP_D0_SCLK: J5.3, J9.7, J10.10, U1.13
/DISP_D1_DIN: J5.5, J9.8, J10.11, U1.16
/DISP_DC: J9.4, J10.9, U1.27
/DISP_RESET: J9.16, J10.8, U1.28
/ENCODER_A: J3.2, R3.2, SW3.A, U1.30
/ENCODER_B: J3.3, R4.2, SW3.B, U1.31
/ENCODER_SW: J3.4, R6.2, SW3.S2, U1.24
/ESP_GPIO26: JP6.2, JP7.2, JP11.2, U1.11
/ESP_MISO: J5.4, J10.5, U1.14
/ESP_RXD: J4.4, U1.34
/ESP_TXD: J4.5, U1.35
/G_TERM: C24.2, J11.1, Q6.1, R47.2
/I2C_SCL: J6.4, R8.2, U1.36, U2.12, U5.1, U7.4, U8.2
/I2C_SDA: J6.3, R7.2, U1.33, U2.13, U5.6, U7.3, U8.3
/MCP23017_A0: JP1.2, U2.15
/MCP23017_A1: JP2.2, U2.16
/MCP23017_A2: JP3.2, U2.17
/MCP23017_GPA0: D11.2, J8.2, U2.21, U9.1
/MCP23017_GPA1: D12.2, J8.3, U2.22, U10.1
/MCP23017_GPA2: D13.2, J8.4, U2.23, U11.1
/MCP23017_GPA3: D14.2, J8.5, U2.24, U12.1
/MCP23017_GPA4: D15.2, J8.6, U2.25, U13.1
/MCP23017_GPA5: D16.2, J8.7, U2.26, U14.1
/MCP23017_GPA6: D17.2, J8.8, U2.27, U15.1
/MCP23017_GPA7: D18.2, J8.9, U2.28, U16.1
/MCP23017_GPB0: D6.2, J8.17, Q3.1, U2.1
/MCP23017_GPB1: D8.2, J8.16, Q4.1, U2.2
/MCP23017_GPB2: D10.2, J8.15, Q5.1, U2.3
/MCP23017_GPB3: J8.14, U2.4
/MCP23017_GPB4: J8.13, U2.5
/MCP23017_GPB5: J8.12, U2.6
/MCP23017_GPB6: J8.11, JP13.2, U2.7
/MCP23017_GPB7: J8.10, JP10.2, U2.8
/MCP23017_INTA: U1.4, U2.20
/MCP23017_INTB: U1.5, U2.19
/MCP23017_~RESET: R5.2, U1.26, U2.18
/MISC1_TERM: C29.2, J11.6, Q11.1, R52.2
/MISC2_TERM: C30.2, J11.7, Q12.1, R53.2
/MISC3_TERM: C31.2, J11.8, Q13.1, R54.2
/MODE: R2.1, SW2.1, U1.25
/PHOTO: Q1.2, R9.2, U1.8
/PIR: J7.2, U1.12
/RC_TERM: J2.7, J11.9, Q6.2, Q7.2, Q8.2, R39.1, R40.1, R41.1, R55.1, R56.1, R57.1
/RELAY_1_COM_TERM: J12.8, K1.2
/RELAY_1_NC_TERM: J12.7, K1.4
/RELAY_1_NO_TERM: J12.9, K1.3
/RELAY_2_COM_TERM: J12.5, K2.2
/RELAY_2_NC_TERM: J12.4, K2.4
/RELAY_2_NO_TERM: J12.6, K2.3
/RELAY_3_COM_TERM: J12.2, K3.2
/RELAY_3_NC_TERM: J12.1, K3.4
/RELAY_3_NO_TERM: J12.3, K3.3
/RH_TERM: J2.5, J11.10, Q9.2, Q10.2, R42.1, R43.1, R58.1, R59.1
/RMISC_TERM: J2.3, J11.11, Q11.2, Q12.2, Q13.2, R44.1, R45.1, R46.1, R60.1, R61.1, R62.1
/SD_CD: J10.4, JP13.1
/SD_CS: J10.6, JP11.1
/STATUS: D3.1, U1.29
/THERMISTOR_1V1: R13.1, R14.2, R17.2, R19.1
/THERMISTOR_EXT: C20.1, J12.12, R19.2, U1.7
/THERMISTOR_INT: C17.1, R17.1, TH1.1, U1.6
/THERMISTOR_VCC: R13.2, U1.9
/TMP117_ALERT: JP10.1, U5.3
/W1_TERM: C27.2, J11.4, Q9.1, R50.2
/W2_TERM: C28.2, J11.5, Q10.1, R51.2
/Y1_TERM: C25.2, J11.2, Q7.1, R48.2
/Y2_TERM: C26.2, J11.3, Q8.1, R49.2
/~ESP_RESET: C2.1, JP5.2, JP9.1, R1.1, SW1.2, U1.3
GND: C1.1, C2.2, C3.2, C5.2, C6.2, C7.2, C8.2, C9.2, C10.2, C12.2, C13.2, C14.2, C15.2, C16.2, C17.2, C18.2, C19.2, C20.2, C21.2, C22.2, C23.2, D1.4, D2.1, D4.1, H1.1, H2.1, H3.1, H4.1, H5.1, J3.1, J4.1, J5.2, J6.1, J7.1, J8.1, J8.18, J9.1, J9.20, J10.1, J12.11, JP1.1, JP2.1, JP3.1, JP12.1, JP15.1, Q3.2, Q4.2, Q5.2, R9.1, R11.2, R14.1, R20.1, R21.1, R22.1, R23.2, R24.2, R25.2, R26.2, R27.2, R28.2, R29.2, R30.2, R31.2, R32.2, R33.2, R34.2, R35.2, R36.2, R37.2, R38.2, SW1.1, SW2.2, SW3.C, SW3.S1, TH1.2, U1.1, U1.15, U1.38, U1.39, U2.10, U3.1, U3.9, U4.1, U5.2, U6.4, U7.1, U7.7, U8.4
unnamed: C4.1, JP5.1
unnamed: C4.2, J4.6
unnamed: C8.1, U3.6
unnamed: C10.1, JP1.3, JP2.3, JP3.3, JP8.2, U2.9
unnamed: C11.1, U3.7
unnamed: C11.2, L1.1, U3.8
unnamed: C19.1, JP14.2, Q2.2, U6.1
unnamed: C24.1, R55.2
unnamed: C25.1, R56.2
unnamed: C26.1, R57.2
unnamed: C27.1, R58.2
unnamed: C28.1, R59.2
unnamed: C29.1, R60.2
unnamed: C30.1, R61.2
unnamed: C31.1, R62.2
unnamed: D1.3, F1.2, RV1.1
unnamed: D2.2, R12.2
unnamed: D3.2, R15.2
unnamed: D4.2, R16.1
unnamed: D5.2, K1.1, Q3.3
unnamed: D6.1, R20.2
unnamed: D7.2, K2.1, Q4.3
unnamed: D8.1, R21.2
unnamed: D9.2, K3.1, Q5.3
unnamed: D10.1, R22.2
unnamed: D11.1, R23.1
unnamed: D12.1, R24.1
unnamed: D13.1, R25.1
unnamed: D14.1, R26.1
unnamed: D15.1, R27.1
unnamed: D16.1, R28.1
unnamed: D17.1, R29.1
unnamed: D18.1, R30.1
unnamed: F1.1, J2.2, J2.4, J2.6, J2.8
unnamed: J1.1, J2.1
unnamed: J4.2, JP6.1
unnamed: J4.3, JP4.2
unnamed: J5.6, JP7.1
unnamed: JP9.2, U3.4
unnamed: JP12.2, U5.4
unnamed: JP15.2, U7.5
unnamed: Q6.3, R47.1, U9.4
unnamed: Q7.3, R48.1, U10.4
unnamed: Q8.3, R49.1, U11.4
unnamed: Q9.3, R50.1, U12.4
unnamed: Q10.3, R51.1, U13.4
unnamed: Q11.3, R52.1, U14.4
unnamed: Q12.3, R53.1, U15.4
unnamed: Q13.3, R54.1, U16.4
unnamed: R10.2, R11.1, U3.5
unnamed: R31.1, U9.2
unnamed: R32.1, U10.2
unnamed: R33.1, U11.2
unnamed: R34.1, U12.2
unnamed: R35.1, U13.2
unnamed: R36.1, U14.2
unnamed: R37.1, U15.2
unnamed: R38.1, U16.2
unnamed: R39.2, U9.6
unnamed: R40.2, U10.6
unnamed: R41.2, U11.6
unnamed: R42.2, U12.6
unnamed: R43.2, U13.6
unnamed: R44.2, U14.6
unnamed: R45.2, U15.6
unnamed: R46.2, U16.6

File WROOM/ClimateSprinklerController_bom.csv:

Component,Quantity Per PCB,References,Value,MPN1,MPN2,Footprint,Population
1,8,C24 C25 C26 C27 C28 C29 C30 C31,.01 uF,CC0805KRX7R9BB103,,C_0805_2012Metric,
2,11,C2 C4 C10 C11 C17 C18 C19 C20 C21 C22 C23,100 nF,CC0805KRX7R7BB104,,C_0805_2012Metric,
3,1,C7,220 nF,C2012X5R1H224K125AA,,C_0805_2012Metric,
4,1,C8,1 uF,C0805C105K4RACTU,,C_0805_2012Metric,
5,2,C5 C6,4.7 uF,C2012X5R1H475K125AB,,C_0805_2012Metric,
6,1,C1,10 uF,C2012X5R1V106K085AC,,C_0805_2012Metric,
7,2,C9 C12,10 uF,EEE-HP0J100R,,CP_Elec_5x5.8,
8,3,C14 C15 C16,47 uF,GRM32ER61C476KE15L,,C_1210_3225Metric,
9,1,C13,220 uF,EEE-HB0J221AP,,CP_Elec_8x10,
10,1,C3,470 uF,EEV-FK1H471M,,CP_Elec_16x17.5,
11,1,D1,N/A,CD-MBL206SL,,Diode_Bridge_Bourns_CD-MBL2xxS,
12,3,D5 D7 D9,N/A,1N4148W,,D_SOD-123,
13,1,F1,300 mA,2920L030DR,,Fuse_2920_7451Metric,
14,1,J1,7.5 TO 40 V,694106301002,,BarrelJack_Horizontal,
15,2,J11 J12,HVAC,1862039,,PhoenixContact_SPTAF_1_12-3.5-IL_1x12_P3.50mm_Vertical,
16,3,K1 K2 K3,G5Q-1-DC5,G5Q-1-DC5,,Relay_SPDT_Omron-G5Q-1,
17,1,L1,15 uH,7447709150,MSS1210-153MEB,L_Wuerth_WE-PD-Typ-LS,
18,8,Q6 Q7 Q8 Q9 Q10 Q11 Q12 Q13,2N6073B,2N6073BG,,TO-225-3_Vertical,
19,4,Q2 Q3 Q4 Q5,2N7002,2N7002,,SOT-23,
20,1,Q1,TEPT5700,TEPT5700,,LED_D5.0mm_Clear,
21,8,R55 R56 R57 R58 R59 R60 R61 R62,39,ERJ-P06J390V,,R_0805_2012Metric_Pad1.15x1.40mm_HandSolder,
22,1,R15,120,RT0805FRE07120RL,,R_0805_2012Metric_Pad1.15x1.40mm_HandSolder,
23,8,R39 R40 R41 R42 R43 R44 R45 R46,180,RT0805FRE07180RL,,R_0805_2012Metric_Pad1.15x1.40mm_HandSolder,
24,8,R31 R32 R33 R34 R35 R36 R37 R38,270,RT0805FRE07270RL,,R_0805_2012Metric_Pad1.15x1.40mm_HandSolder,
25,3,R20 R21 R22,560,RT0805FRE07560RL,,R_0805_2012Metric_Pad1.15x1.40mm_HandSolder,
26,8,R47 R48 R49 R50 R51 R52 R53 R54,820,RT0805FRE07820RL,,R_0805_2012Metric_Pad1.15x1.40mm_HandSolder,
27,5,R24 R25 R28 R29 R30,1K5,RT0805FRE071K5L,,R_0805_2012Metric_Pad1.15x1.40mm_HandSolder,
28,1,R12,1K6,RT0805FRE071K6L,,R_0805_2012Metric_Pad1.15x1.40mm_HandSolder,
29,2,R26 R27,2K7,RT0805FRE072K7L,,R_0805_2012Metric_Pad1.15x1.40mm_HandSolder,
30,2,R7 R8,3K3,RT0805FRE073K3L,,R_0805_2012Metric_Pad1.15x1.40mm_HandSolder,
31,1,R14,5K,CRCW08055K00JNTA,,R_0805_2012Metric_Pad1.15x1.40mm_HandSolder,
32,1,R16,8K2,RT0805FRE078K2L,,R_0805_2012Metric_Pad1.15x1.40mm_HandSolder,
33,11,R1 R2 R3 R4 R5 R6 R13 R17 R18 R19 R23,10K,RC0805FR-0710KL,,R_0805_2012Metric_Pad1.15x1.40mm_HandSolder,
34,1,R11,24.9K,RT0805FRE0724K9L,,R_0805_2012Metric_Pad1.15x1.40mm_HandSolder,
35,2,R9 R10,100K,RC0805FR-07100KL,,R_0805_2012Metric_Pad1.15x1.40mm_HandSolder,
36,1,RV1,N/A,B72205S0400K101,,RV_Disc_D7mm_W4mm_P5mm,
37,1,SW2,MODE,PTS645VK582LFS,,SW_Tactile_SPST_Angled_PTS645Vx58-2LFS,
38,1,SW3,PEC11S-929K-S0015,PEC11S-929K-S0015,,RotaryEncoder_Bourns_PEC11S-Switch_Vertical_H9.5mm,
39,1,SW1,RESET,PTS645VK582LFS,,SW_Tactile_SPST_Angled_PTS645Vx58-2LFS,
40,1,TH1,10K,NXFT15XH103FA2B100,,PinSocket_1x02_P2.54mm_Vertical,
41,1,U7,BME280,BME280,,Bosch_LGA-8_2.5x2.5mm_P0.65mm_ClockwisePinNumbering,
42,1,U6,DHT22,DHT22,,PinSocket_1x04_P2.54mm_Vertical,
43,1,U1,ESP32-WROOM-32D,ESP32-WROOM-32D,,ESP32-WROOM-32,
44,1,U4,LD1086DT33TR,LD1086DT33TR,,TO-252-2,
45,1,U3,LMR36520,LMR36520ADDAR,,Texas_HSOP-8-1EP_3.9x4.9mm_P1.27mm_ThermalVias,
46,1,U2,MCP23017_SO,MCP23017-E/SO,,SOIC-28W_7.5x17.9mm_P1.27mm,
47,8,U9 U10 U11 U12 U13 U14 U15 U16,MOC3043,MOC3043SM,,SMDIP-6_W9.53mm,
48,1,U8,SHTC3,SHTC3,,AMS_QFN-4-1EP_2x2mm_P0.95mm_EP0.7x1.6mm,
49,1,U5,TMP117,TMP117MAIDRVR,,WSON-6-1EP_2x2mm_P0.65mm_EP1x1.6mm,





Component Groups:,64
Component Count:,158
Fitted Components:,139
Number of PCBs:,1
Total components:,139
Schematic Version:,2
Schematic Date:,2020-08-14
PCB Variant:,udefault
BoM Date:,"Thursday, March 25, 2021 at 01:13:09 AM"
Schematic Source:,ClimateSprinklerController.sch
KiCad Version:,Eeschema (5.1.9-0-10_14)
